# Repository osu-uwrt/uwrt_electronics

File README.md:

# UWRT Electronics
Circuit board designs for the underwater robotics team. Designed in [EAGLE](https://www.autodesk.com/products/eagle/overview) and manufactured / sponsored by [JLCPCB](https://jlcpcb.com/).

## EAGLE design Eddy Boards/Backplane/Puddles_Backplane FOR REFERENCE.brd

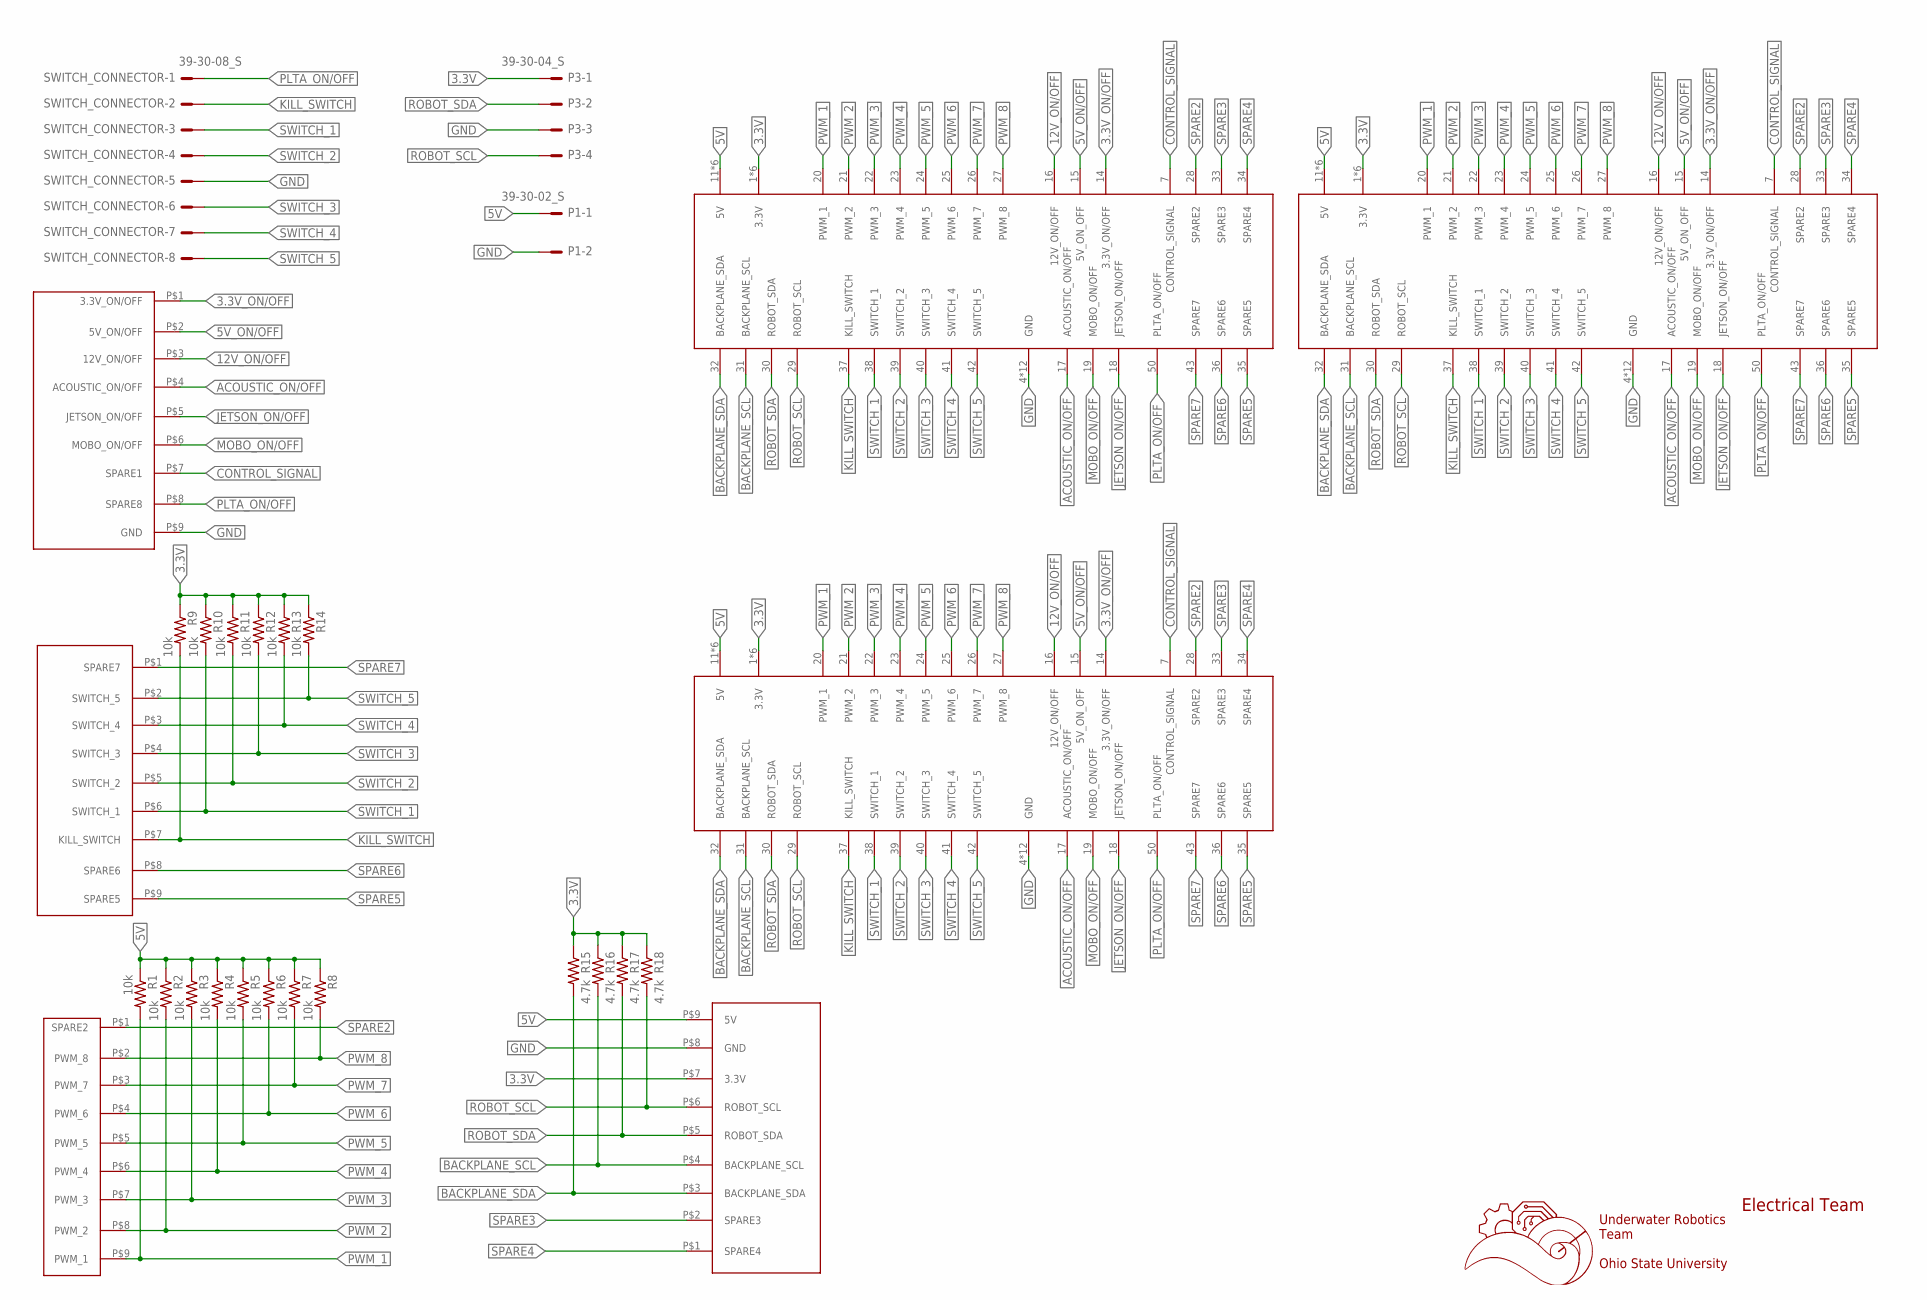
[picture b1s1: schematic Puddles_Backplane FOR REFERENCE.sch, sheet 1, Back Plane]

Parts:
P1: 39-30-02_S; 39-30-?02?
P3: 39-30-04_S; 39-30-?04?
R1, R2, R3, R4, R5, R6, R7, R8, R9, R10, R11, R12, R13, R14: 10k; R0603
R15, R16, R17, R18: 4.7k; R0603
SWITCH_CONNECTOR: 39-30-08_S; 39-30-?08?
U$1, U$2, U$3: 5530843-FEMALE; 5530843-6-BACKPLANEMATE
U$5: 929870-01-09_1; 929852-01-09_1ROW
U$6: 929870-01-09_2; 929852-01-09_1ROW
U$7: 929870-01-09_3; 929852-01-09_1ROW
U$8: 929870-01-09_4; 929852-01-09_1ROW

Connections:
3.3V: P3.1, R9.1, R10.1, R11.1, R12.1, R13.1, R14.1, R15.1, R16.1, R17.1, R18.1, U$1.1 (3.3V), U$1.2 (3.3V), U$1.3 (3.3V), U$1.54 (3.3V), U$1.55 (3.3V), U$1.56 (3.3V), U$2.1 (3.3V), U$2.2 (3.3V), U$2.3 (3.3V), U$2.54 (3.3V), U$2.55 (3.3V), U$2.56 (3.3V), U$3.1 (3.3V), U$3.2 (3.3V), U$3.3 (3.3V), U$3.54 (3.3V), U$3.55 (3.3V), U$3.56 (3.3V), U$8.P$7 (3.3V); also elsewhere on the board
3.3V_ON/OFF: U$1.14 (3.3V_ON/OFF), U$2.14 (3.3V_ON/OFF), U$3.14 (3.3V_ON/OFF), U$7.P$1 (3.3V_ON/OFF)
5V: P1.1, R1.1, R2.1, R3.1, R4.1, R5.1, R6.1, R7.1, R8.1, U$1.11 (5V), U$1.12 (5V), U$1.13 (5V), U$1.44 (5V), U$1.45 (5V), U$1.46 (5V), U$2.11 (5V), U$2.12 (5V), U$2.13 (5V), U$2.44 (5V), U$2.45 (5V), U$2.46 (5V), U$3.11 (5V), U$3.12 (5V), U$3.13 (5V), U$3.44 (5V), U$3.45 (5V), U$3.46 (5V), U$8.P$9 (5V)
5V_ON/OFF: U$1.15 (5V_ON_OFF), U$2.15 (5V_ON_OFF), U$3.15 (5V_ON_OFF), U$7.P$2 (5V_ON/OFF)
12V_ON/OFF: U$1.16 (12V_ON/OFF), U$2.16 (12V_ON/OFF), U$3.16 (12V_ON/OFF), U$7.P$3 (12V_ON/OFF)
ACOUSTIC_ON/OFF: U$1.17 (ACOUSTIC_ON/OFF), U$2.17 (ACOUSTIC_ON/OFF), U$3.17 (ACOUSTIC_ON/OFF), U$7.P$4 (ACOUSTIC_ON/OFF)
BACKPLANE_SCL: R16.2, U$1.31 (BACKPLANE_SCL), U$2.31 (BACKPLANE_SCL), U$3.31 (BACKPLANE_SCL), U$8.P$4 (BACKPLANE_SCL); also elsewhere on the board
BACKPLANE_SDA: R15.2, U$1.32 (BACKPLANE_SDA), U$2.32 (BACKPLANE_SDA), U$3.32 (BACKPLANE_SDA), U$8.P$3 (BACKPLANE_SDA); also elsewhere on the board
CONTROL_SIGNAL: U$1.7 (CONTROL_SIGNAL), U$2.7 (CONTROL_SIGNAL), U$3.7 (CONTROL_SIGNAL), U$7.P$7 (SPARE1)
GND: P1.2, P3.3, SWITCH_CONNECTOR.5, U$1.4 (GND), U$1.5 (GND), U$1.6 (GND), U$1.8 (GND), U$1.9 (GND), U$1.10 (GND), U$1.47 (GND), U$1.48 (GND), U$1.49 (GND), U$1.51 (GND), U$1.52 (GND), U$1.53 (GND), U$2.4 (GND), U$2.5 (GND), U$2.6 (GND), U$2.8 (GND), U$2.9 (GND), U$2.10 (GND), U$2.47 (GND), U$2.48 (GND), U$2.49 (GND), U$2.51 (GND), U$2.52 (GND), U$2.53 (GND), U$3.4 (GND), U$3.5 (GND), U$3.6 (GND), U$3.8 (GND), U$3.9 (GND), U$3.10 (GND), U$3.47 (GND), U$3.48 (GND), U$3.49 (GND), U$3.51 (GND), U$3.52 (GND), U$3.53 (GND), U$7.P$9 (GND), U$8.P$8 (GND); also elsewhere on the board
JETSON_ON/OFF: U$1.18 (JETSON_ON/OFF), U$2.18 (JETSON_ON/OFF), U$3.18 (JETSON_ON/OFF), U$7.P$5 (JETSON_ON/OFF)
KILL_SWITCH: R9.2, SWITCH_CONNECTOR.2, U$1.37 (KILL_SWITCH), U$2.37 (KILL_SWITCH), U$3.37 (KILL_SWITCH), U$5.P$7 (KILL_SWITCH)
MOBO_ON/OFF: U$1.19 (MOBO_ON/OFF), U$2.19 (MOBO_ON/OFF), U$3.19 (MOBO_ON/OFF), U$7.P$6 (MOBO_ON/OFF)
PLTA_ON/OFF: SWITCH_CONNECTOR.1, U$1.50 (PLTA_ON/OFF), U$2.50 (PLTA_ON/OFF), U$3.50 (PLTA_ON/OFF), U$7.P$8 (SPARE8)
PWM_1: R1.2, U$1.20 (PWM_1), U$2.20 (PWM_1), U$3.20 (PWM_1), U$6.P$9 (PWM_1)
PWM_2: R2.2, U$1.21 (PWM_2), U$2.21 (PWM_2), U$3.21 (PWM_2), U$6.P$8 (PWM_2)
PWM_3: R3.2, U$1.22 (PWM_3), U$2.22 (PWM_3), U$3.22 (PWM_3), U$6.P$7 (PWM_3)
PWM_4: R4.2, U$1.23 (PWM_4), U$2.23 (PWM_4), U$3.23 (PWM_4), U$6.P$6 (PWM_4)
PWM_5: R5.2, U$1.24 (PWM_5), U$2.24 (PWM_5), U$3.24 (PWM_5), U$6.P$5 (PWM_5)
PWM_6: R6.2, U$1.25 (PWM_6), U$2.25 (PWM_6), U$3.25 (PWM_6), U$6.P$4 (PWM_6)
PWM_7: R7.2, U$1.26 (PWM_7), U$2.26 (PWM_7), U$3.26 (PWM_7), U$6.P$3 (PWM_7)
PWM_8: R8.2, U$1.27 (PWM_8), U$2.27 (PWM_8), U$3.27 (PWM_8), U$6.P$2 (PWM_8)
ROBOT_SCL: P3.4, R18.2, U$1.29 (ROBOT_SCL), U$2.29 (ROBOT_SCL), U$3.29 (ROBOT_SCL), U$8.P$6 (ROBOT_SCL); also elsewhere on the board
ROBOT_SDA: P3.2, R17.2, U$1.30 (ROBOT_SDA), U$2.30 (ROBOT_SDA), U$3.30 (ROBOT_SDA), U$8.P$5 (ROBOT_SDA); also elsewhere on the board
SPARE2: U$1.28 (SPARE2), U$2.28 (SPARE2), U$3.28 (SPARE2), U$6.P$1 (SPARE2)
SPARE3: U$1.33 (SPARE3), U$2.33 (SPARE3), U$3.33 (SPARE3), U$8.P$2 (SPARE3)
SPARE4: U$1.34 (SPARE4), U$2.34 (SPARE4), U$3.34 (SPARE4), U$8.P$1 (SPARE4)
SPARE5: U$1.35 (SPARE5), U$2.35 (SPARE5), U$3.35 (SPARE5), U$5.P$9 (SPARE5)
SPARE6: U$1.36 (SPARE6), U$2.36 (SPARE6), U$3.36 (SPARE6), U$5.P$8 (SPARE6)
SPARE7: U$1.43 (SPARE7), U$2.43 (SPARE7), U$3.43 (SPARE7), U$5.P$1 (SPARE7)
SWITCH_1: R10.2, SWITCH_CONNECTOR.3, U$1.38 (SWITCH_1), U$2.38 (SWITCH_1), U$3.38 (SWITCH_1), U$5.P$6 (SWITCH_1)
SWITCH_2: R11.2, SWITCH_CONNECTOR.4, U$1.39 (SWITCH_2), U$2.39 (SWITCH_2), U$3.39 (SWITCH_2), U$5.P$5 (SWITCH_2)
SWITCH_3: R12.2, SWITCH_CONNECTOR.6, U$1.40 (SWITCH_3), U$2.40 (SWITCH_3), U$3.40 (SWITCH_3), U$5.P$4 (SWITCH_3)
SWITCH_4: R13.2, SWITCH_CONNECTOR.7, U$1.41 (SWITCH_4), U$2.41 (SWITCH_4), U$3.41 (SWITCH_4), U$5.P$3 (SWITCH_4)
SWITCH_5: R14.2, SWITCH_CONNECTOR.8, U$1.42 (SWITCH_5), U$2.42 (SWITCH_5), U$3.42 (SWITCH_5), U$5.P$2 (SWITCH_5)

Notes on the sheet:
Underwater Robotics Team Ohio State University
Electrical Team

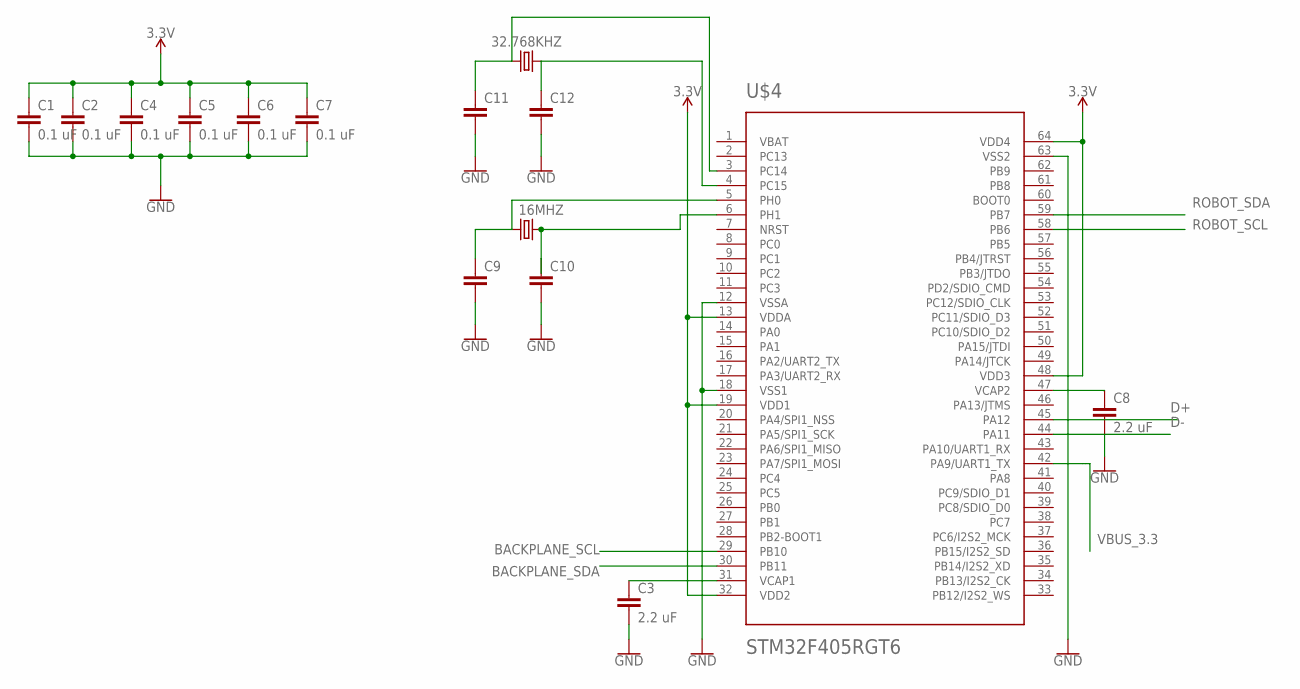
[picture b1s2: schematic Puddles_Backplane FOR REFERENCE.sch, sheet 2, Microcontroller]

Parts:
16MHZ, 32.768KHZ: CRYSTALPTH-HC49US; HC49US
C1, C2, C4, C5, C6, C7: 0.1 uF; C0603
C3, C8: 2.2 uF; C0603
C9, C10, C11, C12: C-EUC0603; C0603
U$4: STM32F405RGT6; TQFP64

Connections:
3.3V: C1.1, C2.1, C4.1, C5.1, C6.1, C7.1, U$4.13 (VDDA), U$4.19 (VDD1), U$4.32 (VDD2), U$4.48 (VDD3), U$4.64 (VDD4); also elsewhere on the board
BACKPLANE_SCL: U$4.29 (PB10); also elsewhere on the board
BACKPLANE_SDA: U$4.30 (PB11); also elsewhere on the board
D+: U$4.45 (PA12); also elsewhere on the board
D-: U$4.44 (PA11); also elsewhere on the board
GND: C1.2, C2.2, C3.2, C4.2, C5.2, C6.2, C7.2, C8.2, C9.2, C10.2, C11.2, C12.2, U$4.12 (VSSA), U$4.18 (VSS1), U$4.63 (VSS2); also elsewhere on the board
unnamed: C3.1, U$4.31 (VCAP1)
unnamed: C8.1, U$4.47 (VCAP2)
unnamed: 16MHZ.1, C9.1, U$4.5 (PH0)
unnamed: 16MHZ.2, C10.1, U$4.6 (PH1)
unnamed: 32.768KHZ.1, C11.1, U$4.3 (PC14)
unnamed: 32.768KHZ.2, C12.1, U$4.4 (PC15)
ROBOT_SCL: U$4.58 (PB6); also elsewhere on the board
ROBOT_SDA: U$4.59 (PB7); also elsewhere on the board
VBUS_3.3: U$4.42 (PA9/UART1_TX); also elsewhere on the board

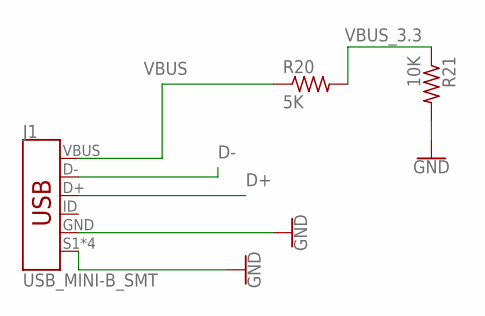
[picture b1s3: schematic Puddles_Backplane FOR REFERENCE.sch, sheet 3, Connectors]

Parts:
J1: USB_MINI-B_SMT; USB-MINIB
R20: 5K; R0603
R21: 10K; R0603

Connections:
D+: J1.D+; also elsewhere on the board
D-: J1.D-; also elsewhere on the board
GND: J1.GND, J1.S1 (SHIELD), J1.S2 (SHIELD), J1.S3 (SHIELD), J1.S4 (SHIELD), R21.2; also elsewhere on the board
VBUS: J1.VBUS, R20.1
VBUS_3.3: R20.2, R21.1; also elsewhere on the board

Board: 2 copper layers, 46 parts (0 on the bottom side), 45 nets, no tracks yet.

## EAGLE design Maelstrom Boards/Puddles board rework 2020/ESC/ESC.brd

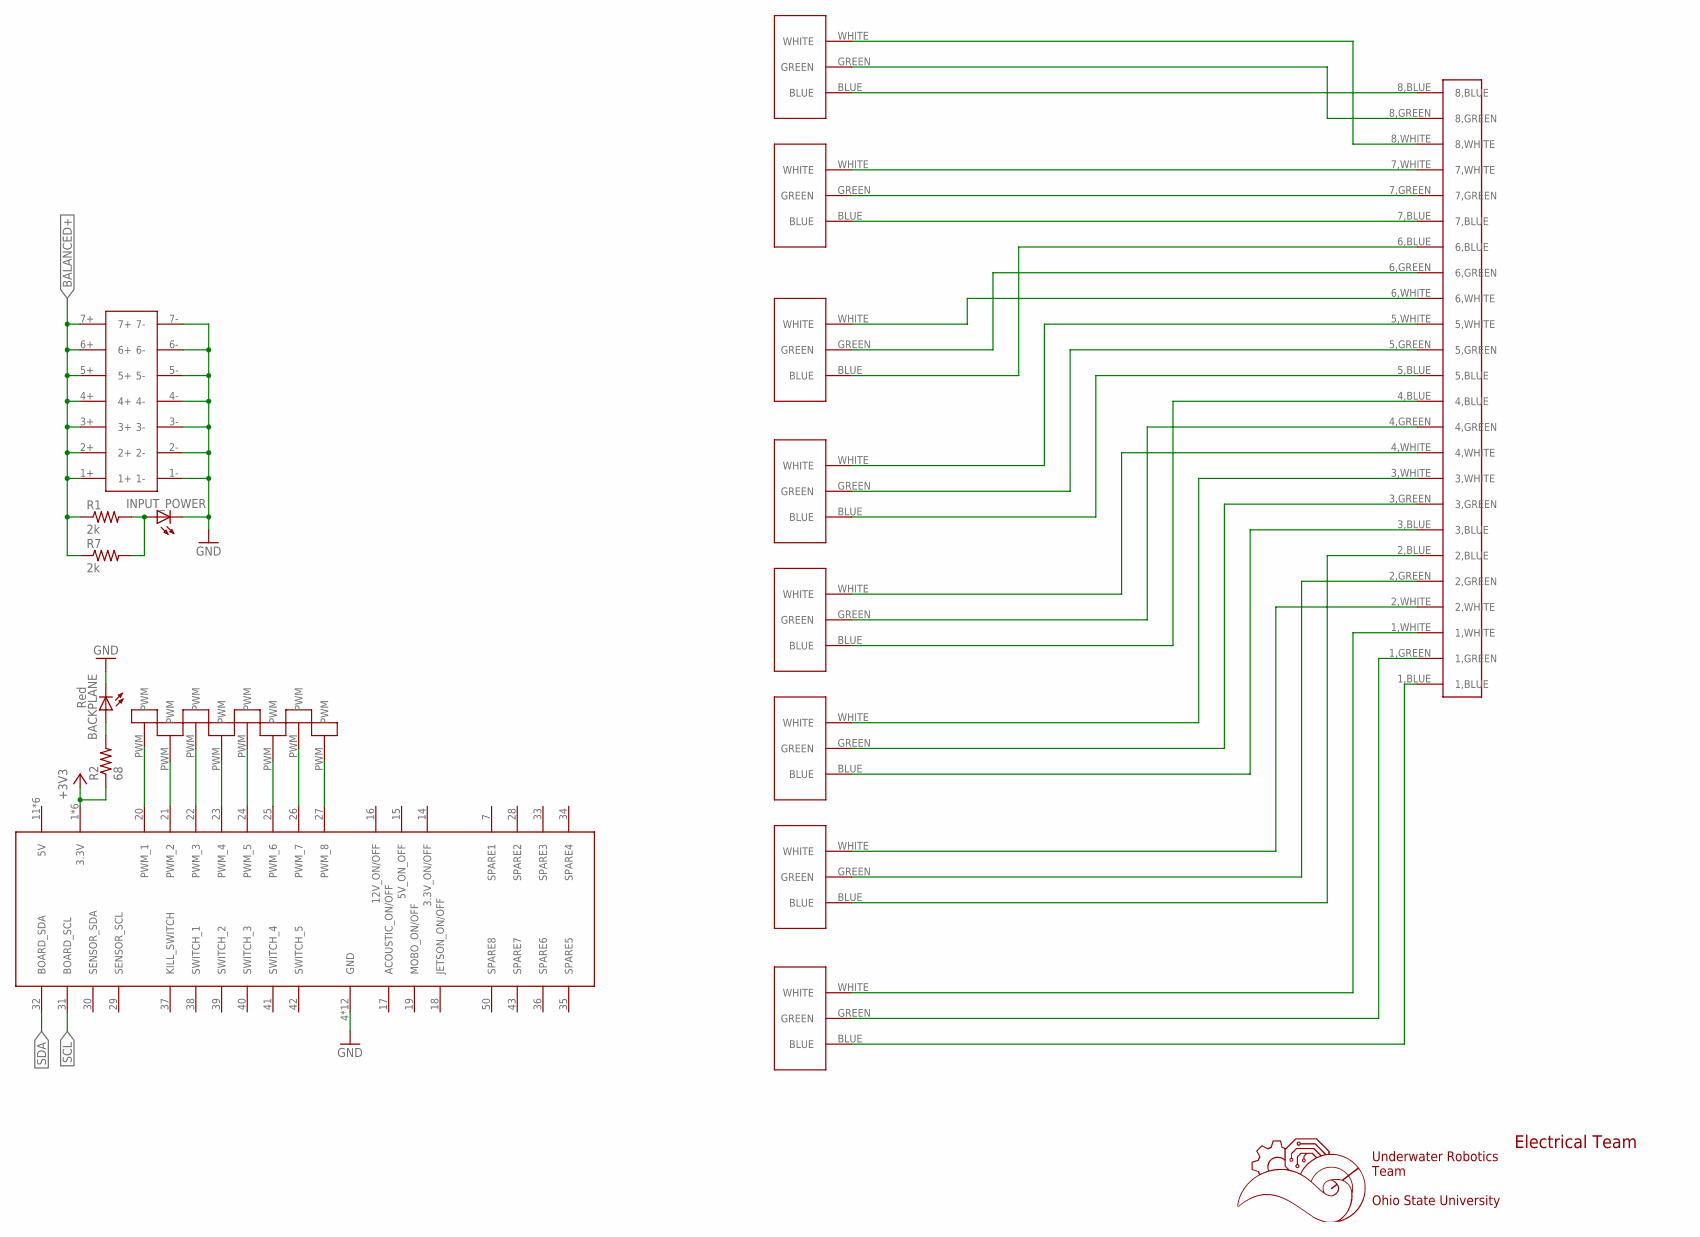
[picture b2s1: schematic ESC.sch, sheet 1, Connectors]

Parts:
1, 2, 3, 4, 5, 6, 7, 8: 1711738
BACKPLANE: Red; CHIPLED_0603
INPUT_POWER: LEDCHIPLED_0603; CHIPLED_0603
P5, P6, P7, P8: MALE1PINHEADER
R1, R7: 2k; R0603
R2: 68; R0603
U$1: 5530843-EDGE; 5530843-6-BOARDFINGERS
U$18: 24PINCONVERTER
U$19: 14PIN_VERT
U$20, U$21, U$22, U$23: MALE1PINHEADER

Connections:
+3V3: R2.1, U$1.1 (3.3V), U$1.2 (3.3V), U$1.3 (3.3V), U$1.54 (3.3V), U$1.55 (3.3V), U$1.56 (3.3V); also elsewhere on the board
BALANCED+: R1.1, R7.1, U$19.1+, U$19.2+, U$19.3+, U$19.4+, U$19.5+, U$19.6+, U$19.7+; also elsewhere on the board
GND: BACKPLANE.C, INPUT_POWER.C, U$1.4 (GND), U$1.5 (GND), U$1.6 (GND), U$1.8 (GND), U$1.9 (GND), U$1.10 (GND), U$1.47 (GND), U$1.48 (GND), U$1.49 (GND), U$1.51 (GND), U$1.52 (GND), U$1.53 (GND), U$19.1-, U$19.2-, U$19.3-, U$19.4-, U$19.5-, U$19.6-, U$19.7-; also elsewhere on the board
unnamed: 1.GREEN, U$18.1,GREEN
unnamed: 8.WHITE, U$18.8,WHITE
unnamed: 8.GREEN, U$18.8,GREEN
unnamed: 8.BLUE, U$18.8,BLUE
unnamed: 7.GREEN, U$18.7,GREEN
unnamed: 7.BLUE, U$18.7,BLUE
unnamed: 6.WHITE, U$18.6,WHITE
unnamed: 6.GREEN, U$18.6,GREEN
unnamed: 6.BLUE, U$18.6,BLUE
unnamed: 5.WHITE, U$18.5,WHITE
unnamed: 5.GREEN, U$18.5,GREEN
unnamed: 5.BLUE, U$18.5,BLUE
unnamed: 4.WHITE, U$18.4,WHITE
unnamed: 4.GREEN, U$18.4,GREEN
unnamed: 4.BLUE, U$18.4,BLUE
unnamed: 3.BLUE, U$18.3,BLUE
unnamed: 3.WHITE, U$18.3,WHITE
unnamed: 3.GREEN, U$18.3,GREEN
unnamed: 2.WHITE, U$18.2,WHITE
unnamed: 2.GREEN, U$18.2,GREEN
unnamed: 2.BLUE, U$18.2,BLUE
unnamed: 1.WHITE, U$18.1,WHITE
unnamed: 7.WHITE, U$18.7,WHITE
unnamed: 1.BLUE, U$18.1,BLUE
unnamed: INPUT_POWER.A, R1.2, R7.2
unnamed: BACKPLANE.A, R2.2
PWM_1: U$1.20 (PWM_1), U$20.PWM
PWM_2: U$1.21 (PWM_2), U$21.PWM
PWM_3: U$1.22 (PWM_3), U$22.PWM
PWM_4: U$1.23 (PWM_4), U$23.PWM
PWM_5: P5.PWM, U$1.24 (PWM_5)
PWM_6: P6.PWM, U$1.25 (PWM_6)
PWM_7: P7.PWM, U$1.26 (PWM_7)
PWM_8: P8.PWM, U$1.27 (PWM_8)
SCL: U$1.31 (BOARD_SCL); also elsewhere on the board
SDA: U$1.32 (BOARD_SDA); also elsewhere on the board

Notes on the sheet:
Underwater Robotics Team Ohio State University
Electrical Team

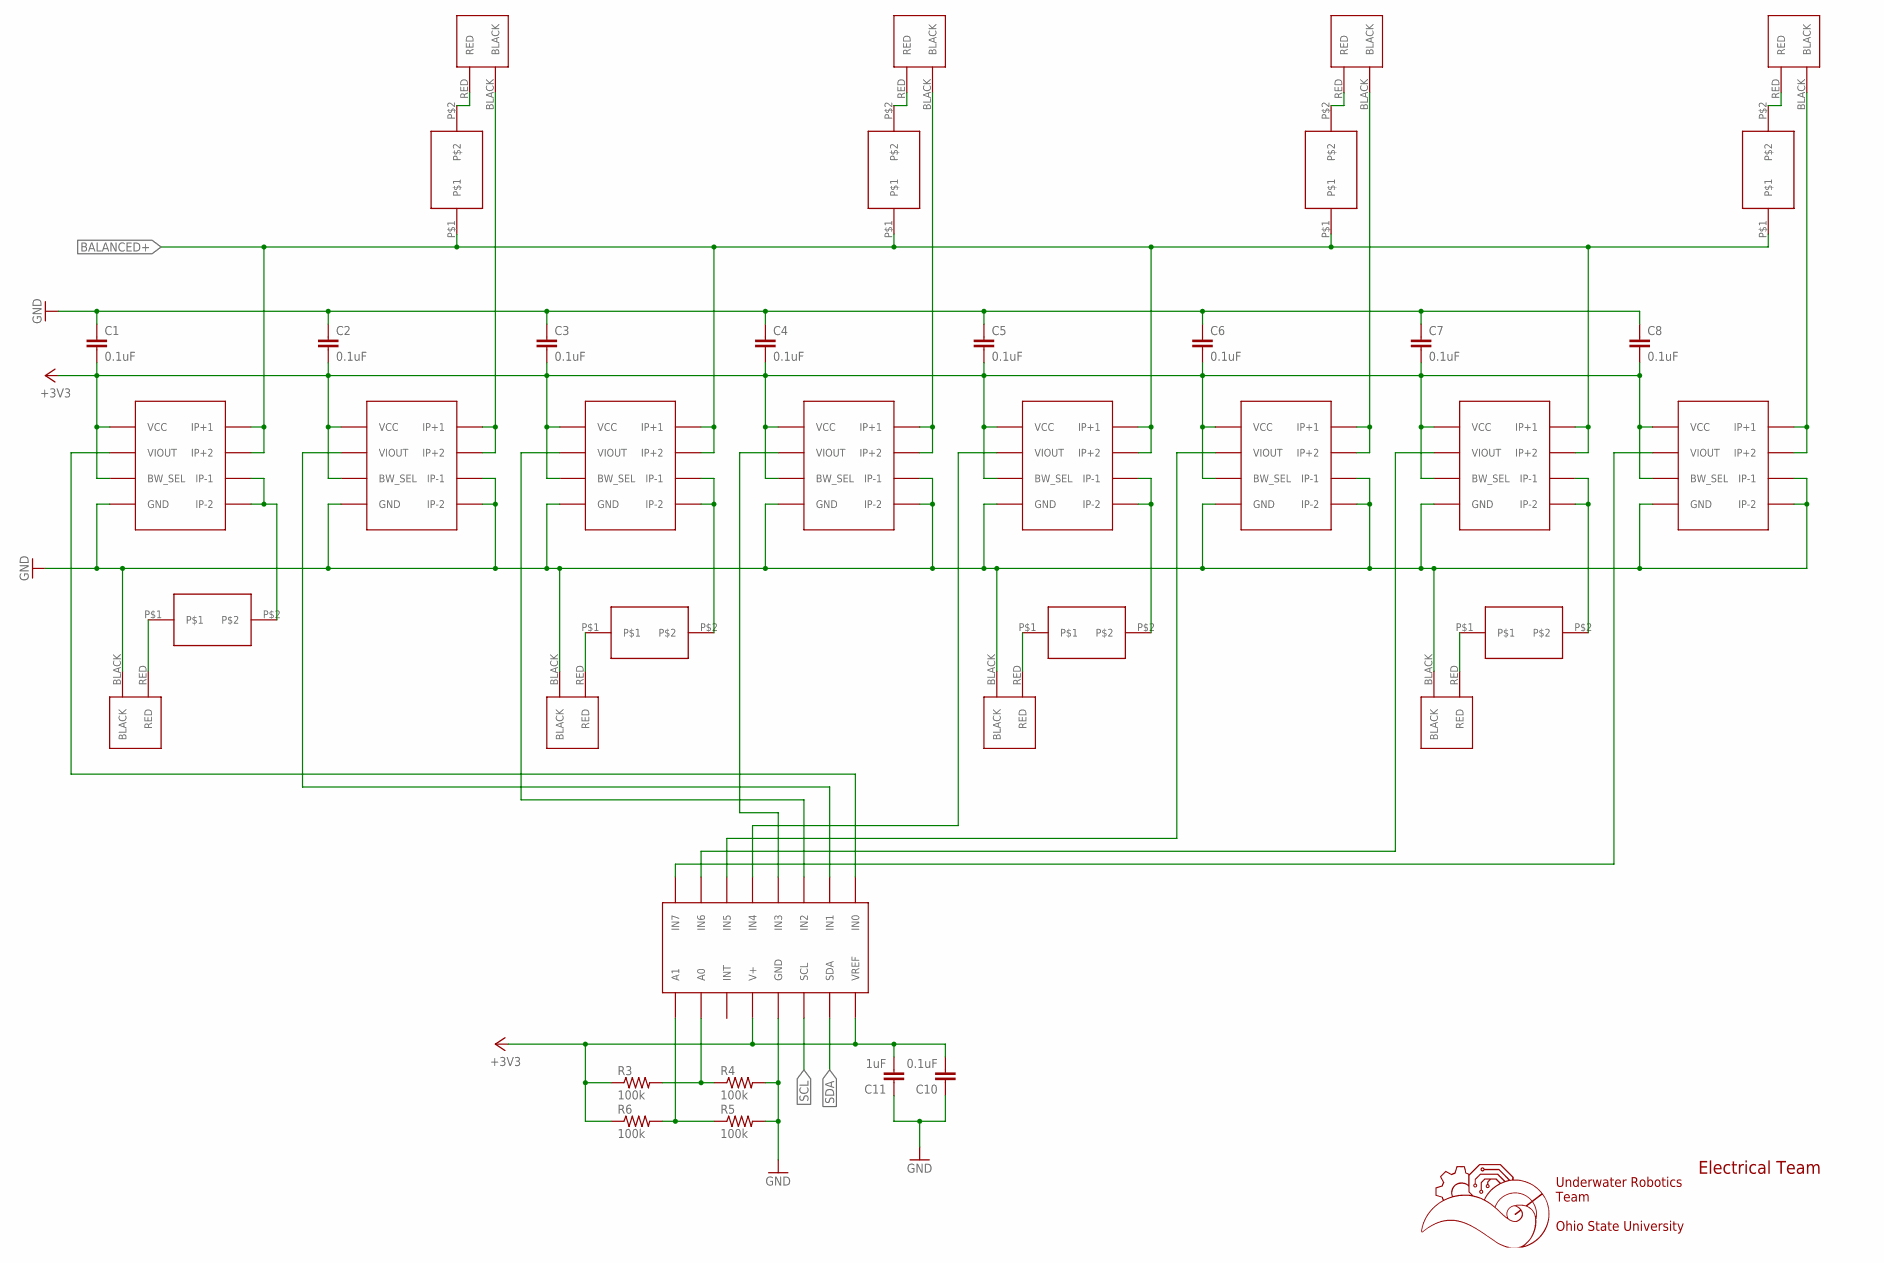
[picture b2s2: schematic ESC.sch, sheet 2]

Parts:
1C, 2C, 3C, 4C, 5C, 6C, 7C, 8C: ACS722; SOIC-8
1CONNECT, 2CONNECT, 3CONNECT, 4CONNECT, 5CONNECT, 7CONNECT, 8CONNECT: 1711725
C1, C2, C3, C4, C5, C6, C7, C8, C10: 0.1uF; C0603
C11: 1uF; C0603
CONNECT: 1711725
R3, R4, R5, R6: 100k; R0603
U$2, U$3, U$4, U$5, U$6, U$7, U$8, U$9: 1206SFH
U$24: ADC128D818; TSSOP-16

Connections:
0ADC: 1C.VIOUT, U$24.IN0
1ADC: 2C.VIOUT, U$24.IN1
2ADC: 3C.VIOUT, U$24.IN2
3ADC: 4C.VIOUT, U$24.IN3
4ADC: 5C.VIOUT, U$24.IN4
5ADC: 6C.VIOUT, U$24.IN5
6ADC: 7C.VIOUT, U$24.IN6
7ADC: 8C.VIOUT, U$24.IN7
+3V3: 1C.BW_SEL, 1C.VCC, 2C.BW_SEL, 2C.VCC, 3C.BW_SEL, 3C.VCC, 4C.BW_SEL, 4C.VCC, 5C.BW_SEL, 5C.VCC, 6C.BW_SEL, 6C.VCC, 7C.BW_SEL, 7C.VCC, 8C.BW_SEL, 8C.VCC, C1.2, C2.2, C3.2, C4.2, C5.2, C6.2, C7.2, C8.2, C10.2, C11.2, R3.1, R6.1, U$24.V+, U$24.VREF; also elsewhere on the board
BALANCED+: 1C.IP+1, 1C.IP+2, 3C.IP+1, 3C.IP+2, 5C.IP+1, 5C.IP+2, 7C.IP+1, 7C.IP+2, U$2.P$1, U$3.P$1, U$4.P$1, U$5.P$1; also elsewhere on the board
GND: 1C.GND, 1CONNECT.BLACK, 2C.GND, 2C.IP-1, 2C.IP-2, 3C.GND, 3CONNECT.BLACK, 4C.GND, 4C.IP-1, 4C.IP-2, 5C.GND, 5CONNECT.BLACK, 6C.GND, 6C.IP-1, 6C.IP-2, 7C.GND, 7CONNECT.BLACK, 8C.GND, 8C.IP-1, 8C.IP-2, C1.1, C2.1, C3.1, C4.1, C5.1, C6.1, C7.1, C8.1, C10.1, C11.1, R4.2, R5.2, U$24.GND; also elsewhere on the board
unnamed: 8C.IP+1, 8C.IP+2, 8CONNECT.BLACK
unnamed: 2CONNECT.RED, U$2.P$2
unnamed: 4CONNECT.RED, U$4.P$2
unnamed: 1C.IP-1, 1C.IP-2, U$6.P$2
unnamed: CONNECT.RED, U$5.P$2
unnamed: 2C.IP+1, 2C.IP+2, 2CONNECT.BLACK
unnamed: 3C.IP-1, 3C.IP-2, U$7.P$2
unnamed: 5C.IP-1, 5C.IP-2, U$8.P$2
unnamed: 4C.IP+1, 4C.IP+2, 4CONNECT.BLACK
unnamed: 6C.IP+1, 6C.IP+2, CONNECT.BLACK
unnamed: 7C.IP-1, 7C.IP-2, U$9.P$2
unnamed: 8CONNECT.RED, U$3.P$2
unnamed: 1CONNECT.RED, U$6.P$1
unnamed: 3CONNECT.RED, U$7.P$1
unnamed: 5CONNECT.RED, U$8.P$1
unnamed: 7CONNECT.RED, U$9.P$1
unnamed: R3.2, R4.1, U$24.A0
unnamed: R5.1, R6.2, U$24.A1
SCL: U$24.SCL; also elsewhere on the board
SDA: U$24.SDA; also elsewhere on the board

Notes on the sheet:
Underwater Robotics Team Ohio State University
Electrical Team

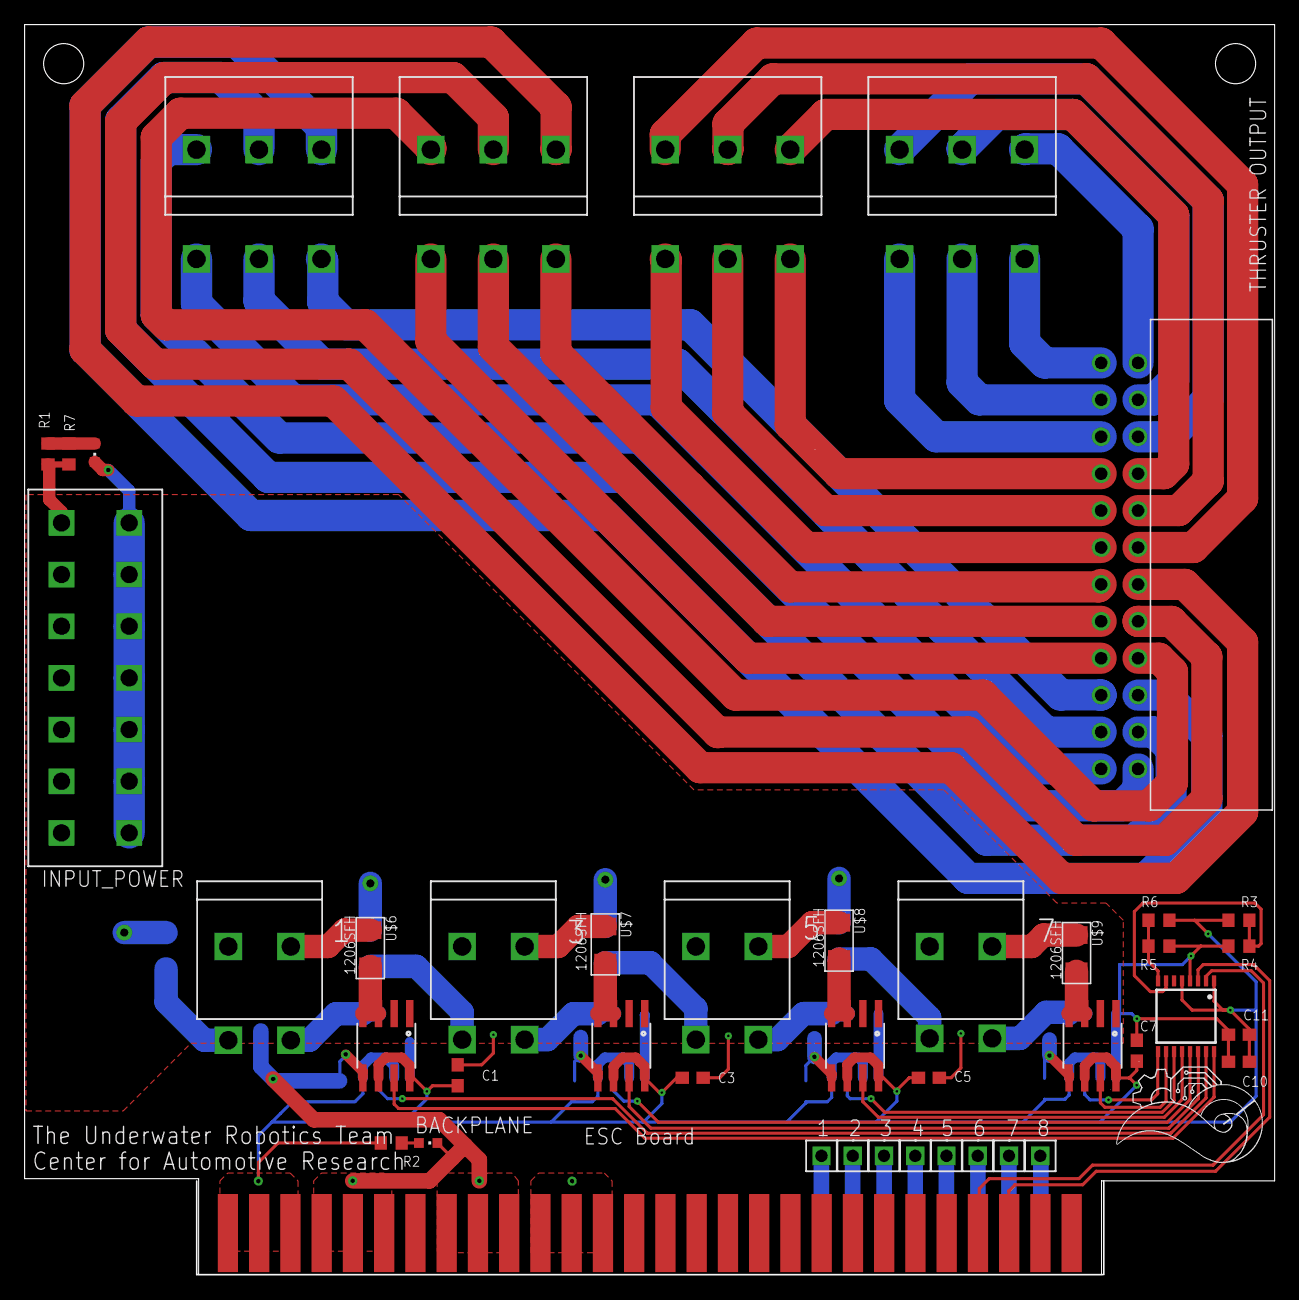
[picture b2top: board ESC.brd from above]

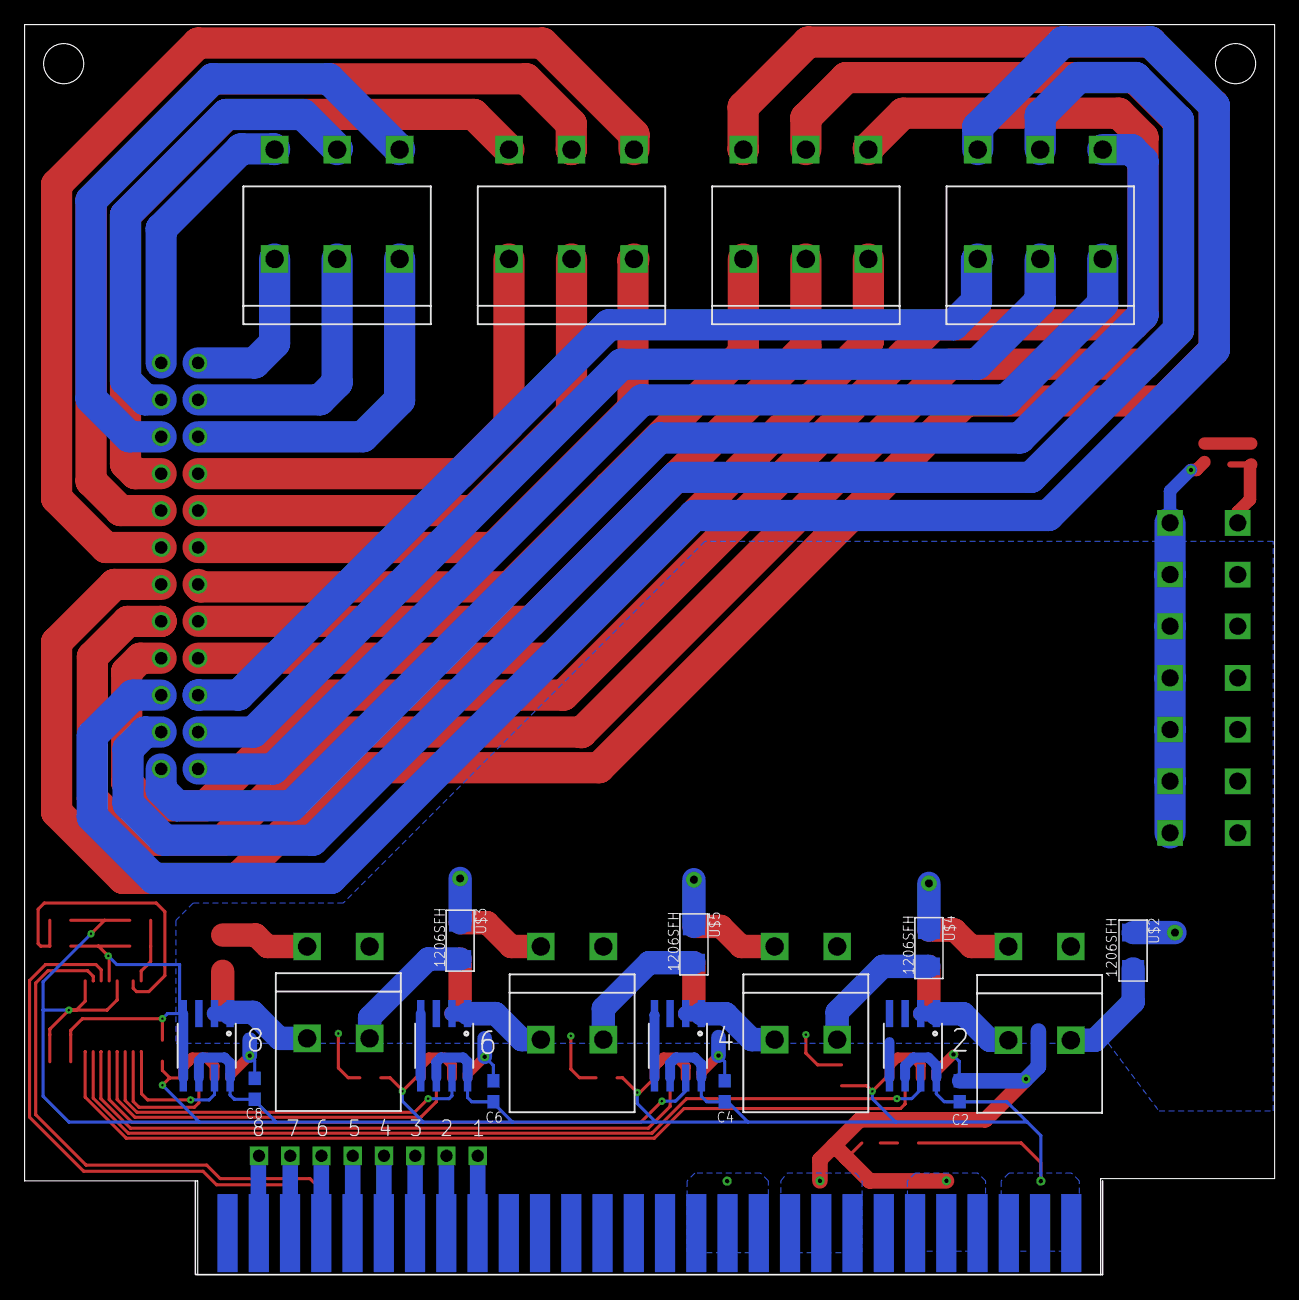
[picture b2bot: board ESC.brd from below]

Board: 2 copper layers, 101.6 x 101.6 mm, 63 parts (20 on the bottom side), 65 nets.

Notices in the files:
parts and their libraries:
SparkFun-Clocks: Licensing: Creative Commons ShareAlike 4.0 International - https://creativecommons.org/licenses/by-sa/4.0
con-molex-mini-fit: Copyright (C) 2011, Bob Starr
COPYRIGHT: Copyright (C) 2018 Accelerated Designs. All rights reserved
